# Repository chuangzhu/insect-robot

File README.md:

__中文 | [English](./README.en.md)__
# Insect Robot
用你的手机控制一只昆虫。  
>This project is greatly inspired by [Backyardbrains/Roboroach](https://github.com/backyardbrains/roboroach).  

## 开始
```Shell
git clone --recursive https://github.com/genelocated/insect-robot.git
```
#### 硬件
用 Eagle 7.7.0 打开 `hard/insect-robot.brd` 文件，选择 `文件 > CAM 处理器...` 。  
`文件 > 打开 > 作业...` , 打开 `gerb274x.cam` , 处理作业。  
打开作业 `excellon.cam` , 处理作业。  
将生成的 gerber 文件发给 pcb 打样厂。

#### 被控端固件

由于主控芯片采用的是 AVR，所以兼容 Arduino。可以使用 Arduino IDE 编程，具体请见 [arduino](./arduino/) 目录。

另一种方法：用 atmel studio 打开 `avr/controlled/insectRobot.atsln` , 运行 `build > build solution` 。  
生成的 hex 文件为 `Debug/controlled.hex` , 用 avrdude 或 progisp 烧录。需要用到 AVR asp。  
你还需要买一块 [FPC 6p 转接板](https://s.taobao.com/search?q=fpc+转接板+直插)。

#### 手机端
用微信扫描以下二维码打开小程序：  
</img>

## 许可协议
本项目为开源硬件项目。

该项目本身采用[知识共享署名-相同方式共享 4.0 国际许可协议](https://creativecommons.org/licenses/by-sa/4.0/deed.zh)进行许可。  
小程序使用 MIT 协议进行许可。

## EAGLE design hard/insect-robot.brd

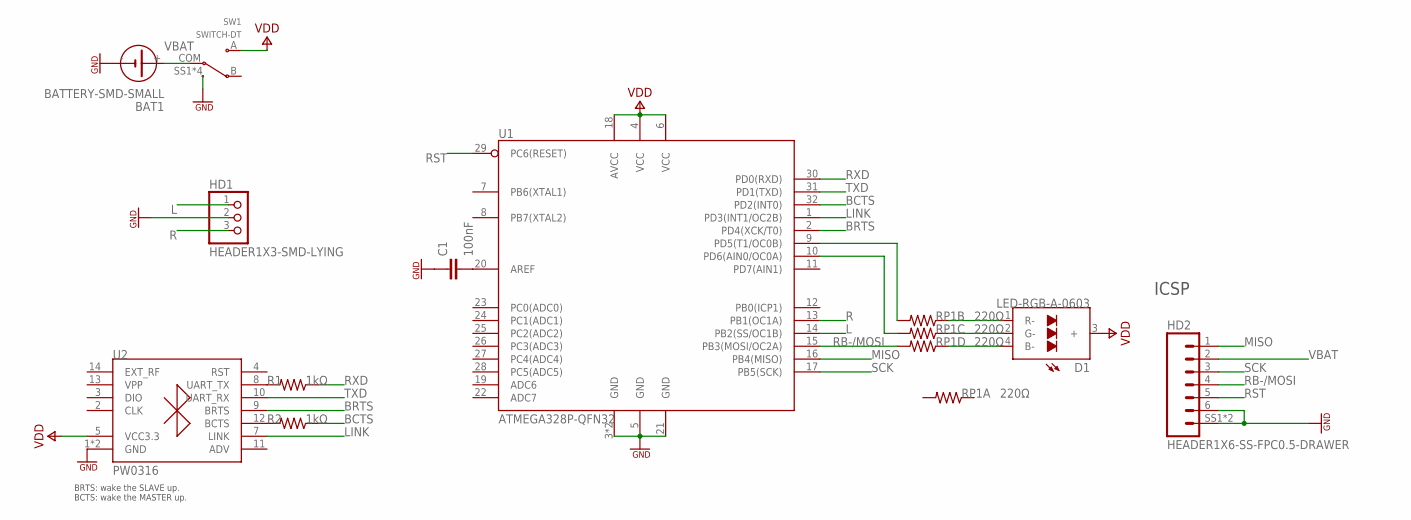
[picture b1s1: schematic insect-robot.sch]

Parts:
BAT1: BATTERY-SMD-SMALL; BAT-SMD-SMALL
C1: 100nF; SMD0603
D1: LED-RGB-A-0603; LED-0603X2
HD1: HEADER1X3-SMD-LYING; SMD-1X3-LYING
HD2: HEADER1X6-SS-FPC0.5-DRAWER; FPC0.5-6-DRAWER
R1, R2: 1kΩ; SMD0603
RP1: 220Ω; RP0603
SW1: SWITCH-DT; SWITCH-SMD-6.7X2.7
U1: ATMEGA328P-QFN32; QFN32
U2: PW0316

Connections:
AREF: C1.2, U1.20 (AREF)
B-: D1.4 (B-), RP1.7 (1)
BCTS: R2.1, U1.32 (PD2(INT0))
BRTS: U1.2 (PD4(XCK/T0)), U2.9 (BRTS)
G-: D1.2 (G-), RP1.5 (1)
GND: BAT1.-, C1.1, HD1.2, HD2.6, HD2.SS1 (7), HD2.SS2 (7), SW1.SS1 (SS), SW1.SS2 (SS), SW1.SS3 (SS), SW1.SS4 (SS), U1.3 (GND), U1.5 (GND), U1.21 (GND), U1.EP (GND), U2.1 (GND), U2.6 (GND)
L: HD1.1, U1.14 (PB2(SS/OC1B))
LINK: U1.1 (PD3(INT1/OC2B)), U2.7 (LINK)
MISO: HD2.1, U1.16 (PB4(MISO))
R: HD1.3, U1.13 (PB1(OC1A))
R-: D1.1 (R-), RP1.3 (1)
R-BCTS: R2.2, U2.12 (BCTS)
R-TX: R1.2, U2.8 (UART_TX)
RB-/MOSI: HD2.4, RP1.8 (2), U1.15 (PB3(MOSI/OC2A))
RG-: RP1.6 (2), U1.10 (PD6(AIN0/OC0A))
RR-: RP1.4 (2), U1.9 (PD5(T1/OC0B))
RST: HD2.5, U1.29 (PC6(RESET))
RXD: R1.1, U1.30 (PD0(RXD))
SCK: HD2.3, U1.17 (PB5(SCK))
TXD: U1.31 (PD1(TXD)), U2.10 (UART_RX)
VBAT: BAT1.+, HD2.2, SW1.COM
VDD: D1.3 (+), SW1.A, U1.4 (VCC), U1.6 (VCC), U1.18 (AVCC), U2.5 (VCC3.3)

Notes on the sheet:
ICSP
BRTS: wake the SLAVE up. BCTS: wake the MASTER up.

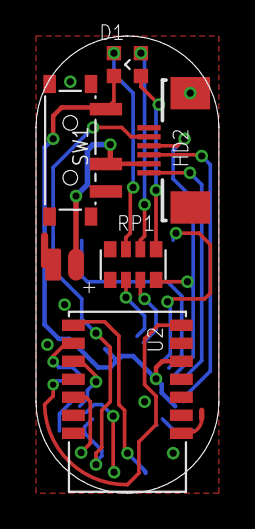
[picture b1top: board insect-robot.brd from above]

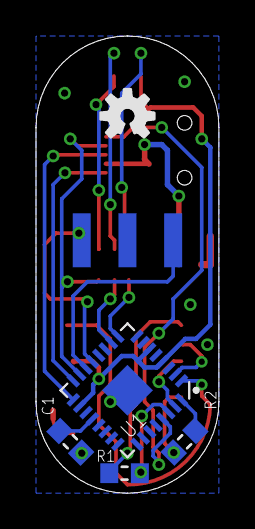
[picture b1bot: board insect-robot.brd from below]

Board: 2 copper layers, 10.2 x 25.4 mm, 12 parts (6 on the bottom side), 22 nets.

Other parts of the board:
OSHW: ICON-OSHW

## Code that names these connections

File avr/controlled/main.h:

/*
 * main.h
 *
 * Created: 2018/4/28 22:28:03
 *  Author: geneLocated
 */ 


#ifndef MAIN_H_
#define MAIN_H_

#include <avr/io.h>
#include <avr/interrupt.h>
#include <util/delay.h>
#include <stdlib.h>
#include <string.h>
#include "../lib/USART/HAL_USART.h"
#include "../lib/ADC/HAL_ADC.h"

//Pins definitions.
#define RXD		PORTD0
#define TXD		PORTD1
#define BCTS	PORTD2
#define LINK	PORTD3
#define BRTS	PORTD4

#define eleLeft		PORTB2
#define eleRight	PORTB1

//This commit corrected LED to PWM pins,
#define ledR PORTD5	//OC0B
#define ledG PORTD6	//OC0A
#define ledB PORTB3	//OC2A

#define PWM_0B_ENABLE
#define PWM_0A_ENABLE
#define PWM_2A_ENABLE
#include "../lib/PWM/HAL_PWM.h"

#define set(Reg, Bit)	Reg |= (1<<Bit)		//Set a bit of reg.
#define clr(Reg, Bit)	Reg &= ~(1<<Bit)	//Clear a bit of reg.
#define not(Reg, Bit)	Reg ^= (1<<Bit)		//Reverse a bit of reg.

unsigned char ledDuty[3];

#define elePeriod	30		//*10us
#define eleDuty		20		//*10us
#define eleTimeout	1000	//*10us

unsigned char pwmElePin;

#endif /* MAIN_H_ */

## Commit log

2018-03-03 Add MCU and battery
2018-03-03 Add bluetooth module
2018-03-31 Add MOSFET for charging control
2018-03-31 Add ISP programming port
2018-03-31 Add RGB LED
2018-03-31 Connect pins
2018-03-31 Create board
2018-04-01 Place the components
2018-04-01 Place components
2018-04-01 Redraw some components
2018-04-01 Route some wires
2018-04-01 Done routing
2018-04-01 Place labels
2018-04-05 Relocate some components
2018-04-14 Redesign
2018-04-14 Redesign finished
2018-04-14 Wechat mini program init
2018-04-21 Fixed RGB LED footprint
2018-04-22 Add beetle animation
2018-04-22 Add devices page, bluetooth
2018-04-22 Add search bluetooth
2018-04-22 Add create BLE connection
2018-04-25 Remove sensitive data
2018-04-28 Firmware init
2018-04-28 Add AVR lib submodule
2018-04-28 Add .gitattributes
2018-04-30 Using BLE module, I can control LED now
2018-05-01 Add LED PWM
2018-05-01 Get a random color on start
2018-05-01 Now get more random :laughing:
2018-05-01 Simple implementation of electrode
2018-05-01 More complex implementation
2018-05-04 Wechat mini program design
2018-05-05 Add write characterist
2018-05-05 Add module rename
2018-05-06 Try to add color for insect separating in wechat
2018-05-07 Device color sharing
2018-05-11 Optimise UI
2018-05-12 Add new mode to fix ble devices refresh
2018-05-12 Add get service and characteristic to forbid writing uuid in program directly
2018-05-12 Add credits
2018-05-13 Hi-Z state if both DDR and PORT is low
2018-05-16 Add cooling down time in wechat
2018-05-19 Electrode pwm
2018-05-19 Add README
2018-05-19 Github does not support css in markdown
2018-05-20 Readme add images
2018-06-03 PWM pins
2018-06-03 Remove non-PWM elctrode pins
2018-06-03 LED __hardware__ PWM
2018-06-05 Fix TIMER1
2018-06-05 Correct comments
2018-06-05 Arduino init
2018-06-05 Add setup()
2018-06-05 Add serialEvent
2018-06-05 Add impulse wave generate
2018-06-05 Add comment graph
2018-06-05 Fix avr
2018-06-06 Add arduino chinese readme
2018-06-06 Add arduino english readme
2018-06-06 Which write button
2018-06-06 Update README for arduino
2018-06-18 Fix electrode pins
2018-06-18 Fix common anode led in SCH
2018-06-23 Create LICENSE
2018-06-23 Fix color reversing display
2018-06-24 Cancel using TIMER1
2018-06-30 Arduino readme USBtinyISP
2018-06-30 Add adapter scheme
2018-06-30 Add ISP adaptor board
2018-07-25 Remove get user info
2018-07-25 Add github link in mini program
2018-07-25 Add try console
2018-07-25 Optimise wechat mini
2018-07-25 Show other devices
2018-07-25 Replace with navigators and page parameters
2018-07-25 Add color displaying in console
2018-07-25 Add copy link
2018-07-29 Optimise using button type
2018-07-30 Add devices multilang
2018-07-30 Multilang for all pages
2018-07-30 Add change language
2018-07-30 Finish multilang

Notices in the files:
README.md:
https://mirrors.creativecommons.org/presskit/buttons/88x31/svg/by-sa.svg
